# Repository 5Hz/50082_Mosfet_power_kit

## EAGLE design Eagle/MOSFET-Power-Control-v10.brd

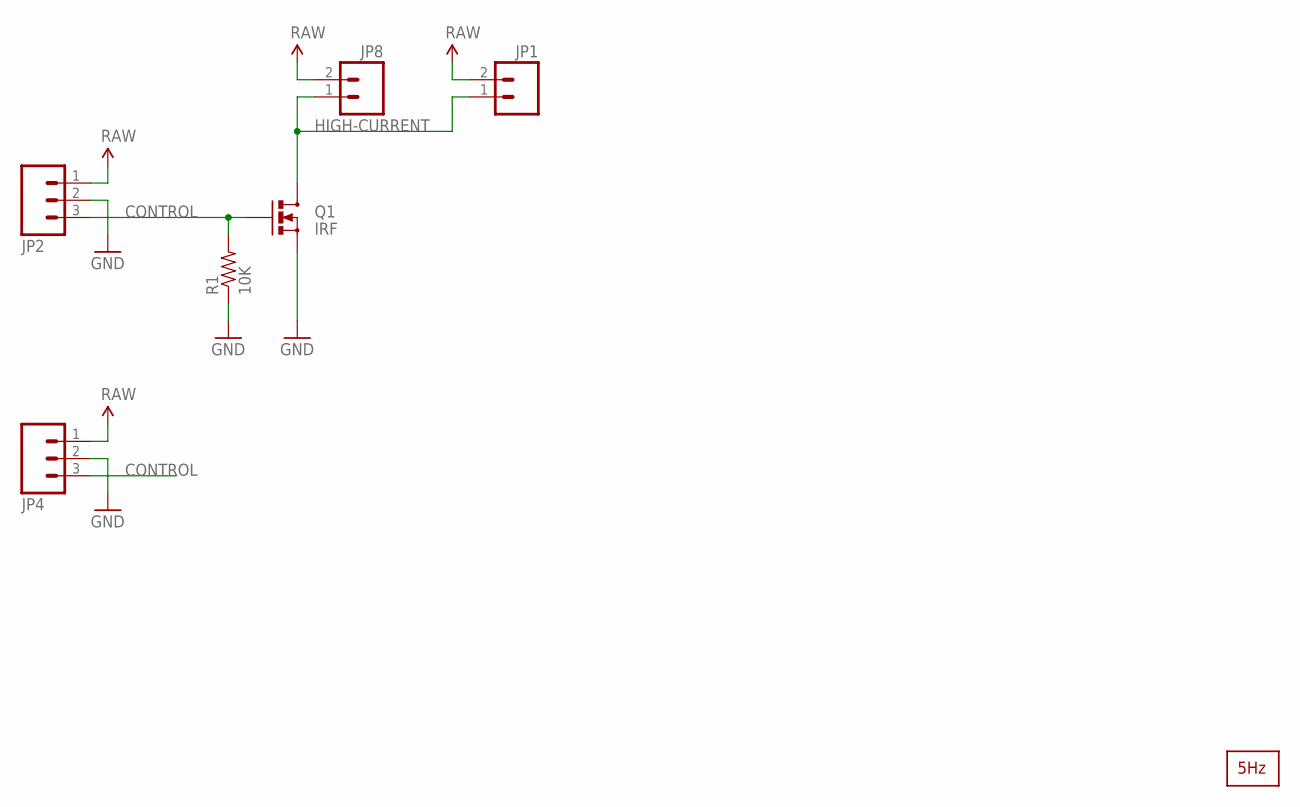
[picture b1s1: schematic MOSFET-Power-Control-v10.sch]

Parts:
JP1: M023.5MM; SCREWTERMINAL-3.5MM-2
JP2: M03JST-PTH; JST-3-PTH
JP4: M03SCREW; SCREWTERMINAL-3.5MM-3
JP8: M02JST-PTH-2; JST-2-PTH
Q1: IRF; TO220V
R1: 10K; AXIAL-0.3
U$1: LOGO2_SILK5MM; LOGO2_5MM

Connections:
CONTROL: JP2.3, JP4.3, Q1.1 (G), R1.P$2 (2)
GND: JP2.2, JP4.2, Q1.3 (S), R1.P$1 (1)
HIGH-CURRENT: JP1.1, JP8.1, Q1.2 (D)
VCC: JP1.2, JP2.1, JP4.1, JP8.2

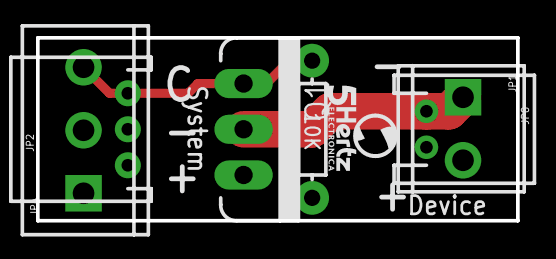
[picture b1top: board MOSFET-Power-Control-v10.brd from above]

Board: 2 copper layers, 26.7 x 10.2 mm, 7 parts (0 on the bottom side), 4 nets.

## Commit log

2014-01-13 creación
